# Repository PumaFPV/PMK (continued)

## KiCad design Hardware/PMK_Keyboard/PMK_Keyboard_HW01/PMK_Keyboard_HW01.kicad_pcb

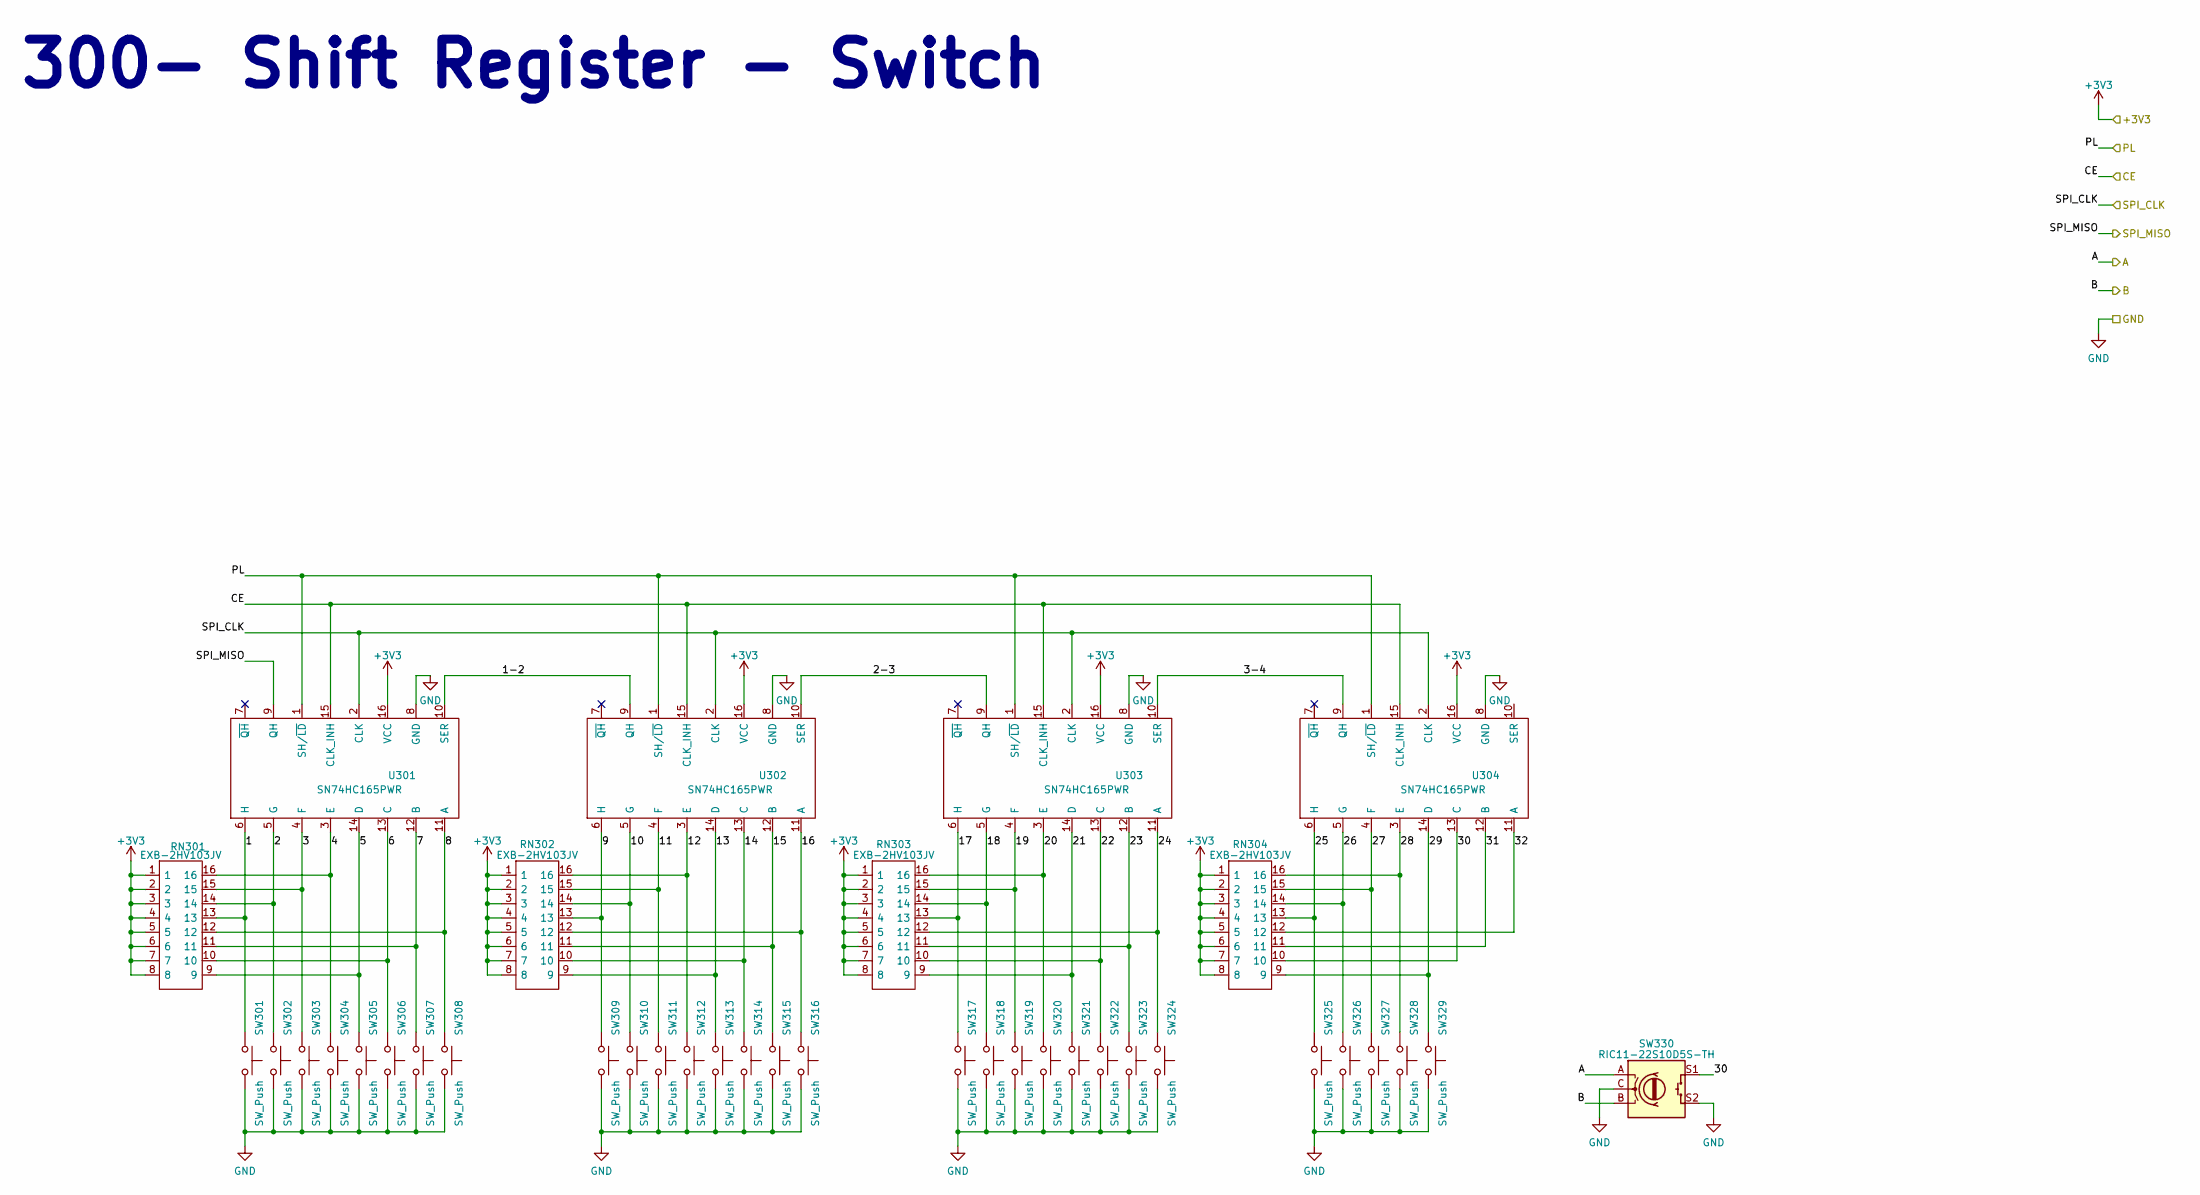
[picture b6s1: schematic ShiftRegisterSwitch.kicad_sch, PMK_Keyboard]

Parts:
RN301, RN302, RN303, RN304: EXB-2HV103JV; EXB2HV_1; Mouser Part Number 667-EXB-2HV103JV
SW301, SW302, SW303, SW304, SW305, SW306, SW307, SW308, SW309, SW310, SW311, SW312, SW313, SW314, SW315, SW316, SW317, SW318, SW319, SW320, SW321, SW322, SW323, SW324, SW325, SW326, SW327, SW328, SW329: SW_Push; Kailh_socket_PG1350_reversible
SW330: RIC11-22S10D5S-TH
U301, U302, U303, U304: SN74HC165PWR; SOP65P640X120-16N; Mouser Part Number 595-SN74HC165PWR

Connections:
+3V3: RN301.1, RN301.2, RN301.3, RN301.4, RN301.5, RN301.6, RN301.7, RN301.8, RN302.1, RN302.2, RN302.3, RN302.4, RN302.5, RN302.6, RN302.7, RN302.8, RN303.1, RN303.2, RN303.3, RN303.4, RN303.5, RN303.6, RN303.7, RN303.8, RN304.1, RN304.2, RN304.3, RN304.4, RN304.5, RN304.6, RN304.7, RN304.8, U301.16 (VCC), U302.16 (VCC), U303.16 (VCC), U304.16 (VCC); also elsewhere on the board
/100- PSoM/A: SW330.A; also elsewhere on the board
/100- PSoM/B: SW330.B; also elsewhere on the board
/100- PSoM/PL: U301.1 (SH/~LD), U302.1 (SH/~LD), U303.1 (SH/~LD), U304.1 (SH/~LD); also elsewhere on the board
/100- PSoM/SPI_CLK: U301.2 (CLK), U302.2 (CLK), U303.2 (CLK), U304.2 (CLK); also elsewhere on the board
/100- PSoM/SPI_MISO: U301.9 (QH); also elsewhere on the board
/100- PSoM/SR_CE: U301.15 (CLK_INH), U302.15 (CLK_INH), U303.15 (CLK_INH), U304.15 (CLK_INH); also elsewhere on the board
/300- Shift Register - Switch/1: RN301.13, SW301.1, U301.6 (H)
/300- Shift Register - Switch/1-2: U301.10 (SER), U302.9 (QH)
/300- Shift Register - Switch/2: RN301.14, SW302.1, U301.5 (G)
/300- Shift Register - Switch/2-3: U302.10 (SER), U303.9 (QH)
/300- Shift Register - Switch/3: RN301.15, SW303.1, U301.4 (F)
/300- Shift Register - Switch/3-4: U303.10 (SER), U304.9 (QH)
/300- Shift Register - Switch/4: RN301.16, SW304.1, U301.3 (E)
/300- Shift Register - Switch/5: RN301.9, SW305.1, U301.14 (D)
/300- Shift Register - Switch/6: RN301.10, SW306.1, U301.13 (C)
/300- Shift Register - Switch/7: RN301.11, SW307.1, U301.12 (B)
/300- Shift Register - Switch/8: RN301.12, SW308.1, U301.11 (A)
/300- Shift Register - Switch/9: RN302.13, SW309.1, U302.6 (H)
/300- Shift Register - Switch/10: RN302.14, SW310.1, U302.5 (G)
/300- Shift Register - Switch/11: RN302.15, SW311.1, U302.4 (F)
/300- Shift Register - Switch/12: RN302.16, SW312.1, U302.3 (E)
/300- Shift Register - Switch/13: RN302.9, SW313.1, U302.14 (D)
/300- Shift Register - Switch/14: RN302.10, SW314.1, U302.13 (C)
/300- Shift Register - Switch/15: RN302.11, SW315.1, U302.12 (B)
/300- Shift Register - Switch/16: RN302.12, SW316.1, U302.11 (A)
/300- Shift Register - Switch/17: RN303.13, SW317.1, U303.6 (H)
/300- Shift Register - Switch/18: RN303.14, SW318.1, U303.5 (G)
/300- Shift Register - Switch/19: RN303.15, SW319.1, U303.4 (F)
/300- Shift Register - Switch/20: RN303.16, SW320.1, U303.3 (E)
/300- Shift Register - Switch/21: RN303.9, SW321.1, U303.14 (D)
/300- Shift Register - Switch/22: RN303.10, SW322.1, U303.13 (C)
/300- Shift Register - Switch/23: RN303.11, SW323.1, U303.12 (B)
/300- Shift Register - Switch/24: RN303.12, SW324.1, U303.11 (A)
/300- Shift Register - Switch/25: RN304.13, SW325.1, U304.6 (H)
/300- Shift Register - Switch/26: RN304.14, SW326.1, U304.5 (G)
/300- Shift Register - Switch/27: RN304.15, SW327.1, U304.4 (F)
/300- Shift Register - Switch/28: RN304.16, SW328.1, U304.3 (E)
/300- Shift Register - Switch/29: RN304.9, SW329.1, U304.14 (D)
/300- Shift Register - Switch/30: RN304.10, SW330.S1, U304.13 (C)
/300- Shift Register - Switch/31: RN304.11, U304.12 (B)
/300- Shift Register - Switch/32: RN304.12, U304.11 (A)
GND: SW301.2, SW302.2, SW303.2, SW304.2, SW305.2, SW306.2, SW307.2, SW308.2, SW309.2, SW310.2, SW311.2, SW312.2, SW313.2, SW314.2, SW315.2, SW316.2, SW317.2, SW318.2, SW319.2, SW320.2, SW321.2, SW322.2, SW323.2, SW324.2, SW325.2, SW326.2, SW327.2, SW328.2, SW329.2, SW330.C, SW330.S2, U301.8 (GND), U302.8 (GND), U303.8 (GND), U304.8 (GND); also elsewhere on the board

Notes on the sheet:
300- Shift Register - Switch

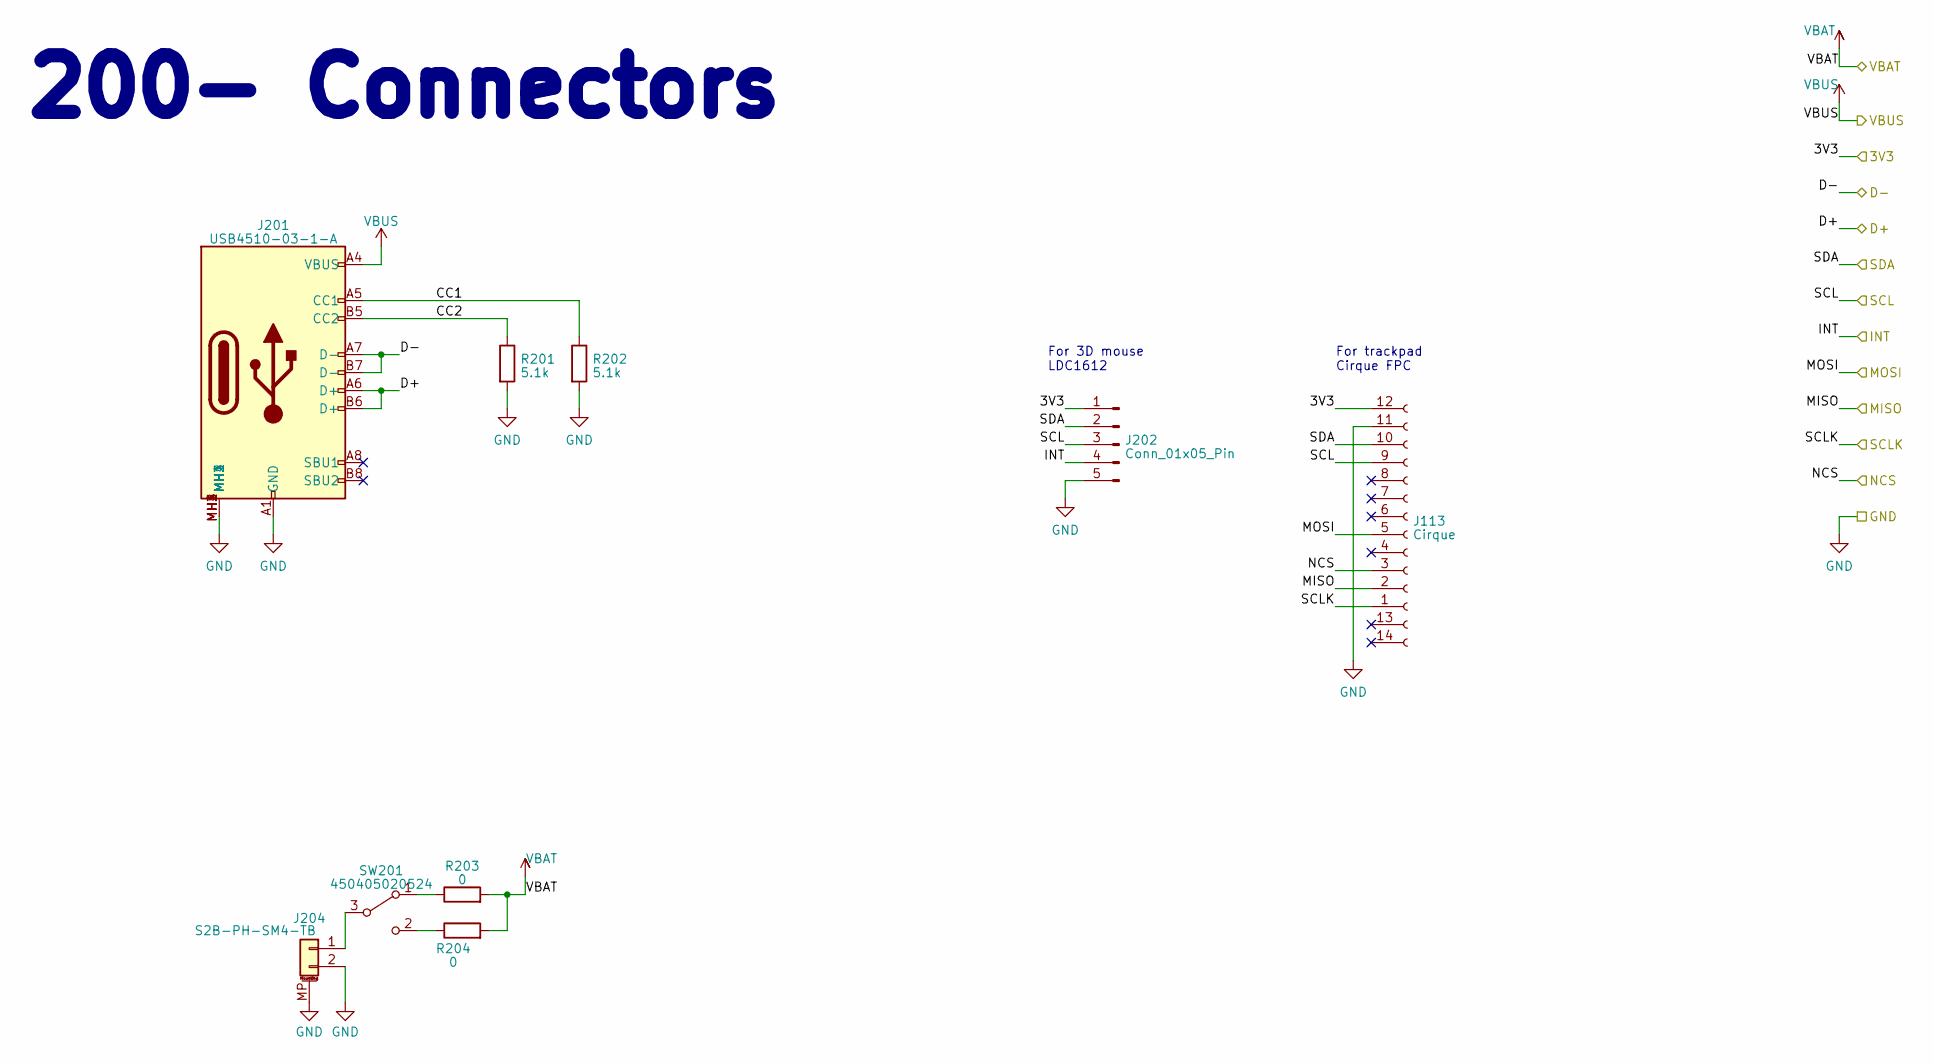
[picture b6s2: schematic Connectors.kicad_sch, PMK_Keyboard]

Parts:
J113: Cirque; Cirque trackpad
J201: USB4510-03-1-A; USB4510031A; Mouser Part Number 640-USB4510031A
J202: Conn_01x05_Pin; SMD_CONN_01x5_1.5mm
J204: S2B-PH-SM4-TB; JST_PH_S2B-PH-SM4-TB_1x02-1MP_P2.00mm_Horizontal_DUALSIDE
R201, R202: 5.1k; R_0201_0603Metric
R203, R204: 0; R_0201_0603Metric
SW201: 450405020524; 450405020524_DUALSIDE

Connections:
+3V3: J202.1; also elsewhere on the board
/100- PSoM/D+: J201.A6 (D+), J201.B6 (D+); also elsewhere on the board
/100- PSoM/D-: J201.A7 (D-), J201.B7 (D-); also elsewhere on the board
/100- PSoM/INT: J202.4; also elsewhere on the board
/100- PSoM/SCL: J202.3; also elsewhere on the board
/100- PSoM/SDA: J202.2; also elsewhere on the board
/200- Connectors/CC1: J201.A5 (CC1), R202.1
/200- Connectors/CC2: J201.B5 (CC2), R201.1
/VBAT: R203.2, R204.2; also elsewhere on the board
GND: J201.A1 (GND), J201.A12 (GND), J201.B1 (GND), J201.B12 (GND), J201.MH1, J201.MH2, J201.MH3, J201.MH4, J202.5, J204.2, J204.MP (MountPin), R201.2, R202.2; also elsewhere on the board
unnamed: J204.1, SW201.3 (B)
unnamed: R203.1, SW201.1 (A)
unnamed: R204.1, SW201.2 (C)
VBUS: J201.A4 (VBUS), J201.A9 (VBUS), J201.B4 (VBUS), J201.B9 (VBUS); also elsewhere on the board

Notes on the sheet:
200- Connectors
For trackpad Cirque FPC
For 3D mouse LDC1612

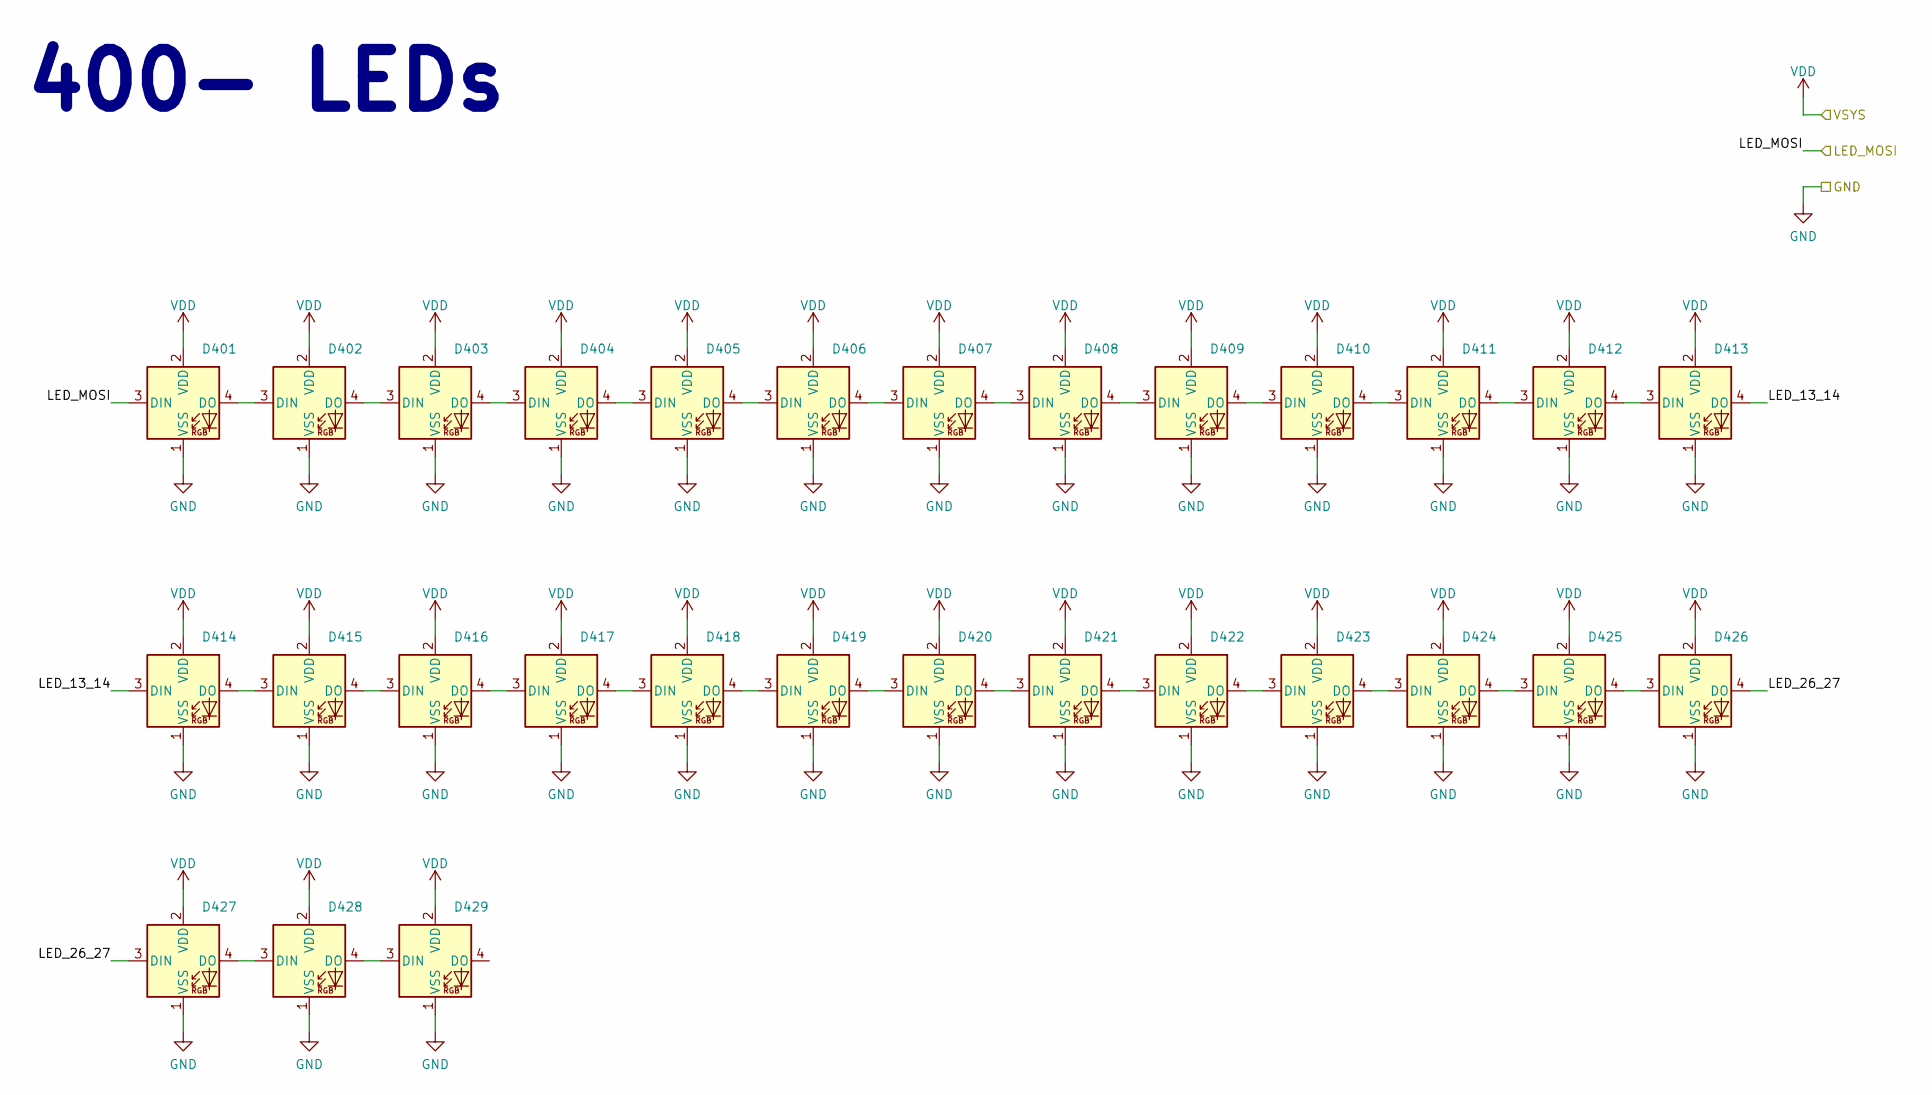
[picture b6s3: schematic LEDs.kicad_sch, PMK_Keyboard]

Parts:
D401, D402, D403, D404, D405, D406, D407, D408, D409, D410, D411, D412, D413, D414, D415, D416, D417, D418, D419, D420, D421, D422, D423, D424, D425, D426, D427, D428, D429: YF923_2020_WS2812_LED; YF923_2020_WS2812_LED_DUALSIDE

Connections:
/100- PSoM/LED_MOSI: D401.3 (DIN); also elsewhere on the board
/400- LEDs/LED_13_14: D413.4 (DO), D414.3 (DIN)
/400- LEDs/LED_26_27: D426.4 (DO), D427.3 (DIN)
GND: D401.1 (VSS), D402.1 (VSS), D403.1 (VSS), D404.1 (VSS), D405.1 (VSS), D406.1 (VSS), D407.1 (VSS), D408.1 (VSS), D409.1 (VSS), D410.1 (VSS), D411.1 (VSS), D412.1 (VSS), D413.1 (VSS), D414.1 (VSS), D415.1 (VSS), D416.1 (VSS), D417.1 (VSS), D418.1 (VSS), D419.1 (VSS), D420.1 (VSS), D421.1 (VSS), D422.1 (VSS), D423.1 (VSS), D424.1 (VSS), D425.1 (VSS), D426.1 (VSS), D427.1 (VSS), D428.1 (VSS), D429.1 (VSS); also elsewhere on the board
unnamed: D401.4 (DO), D402.3 (DIN)
unnamed: D402.4 (DO), D403.3 (DIN)
unnamed: D403.4 (DO), D404.3 (DIN)
unnamed: D404.4 (DO), D405.3 (DIN)
unnamed: D405.4 (DO), D406.3 (DIN)
unnamed: D406.4 (DO), D407.3 (DIN)
unnamed: D407.4 (DO), D408.3 (DIN)
unnamed: D408.4 (DO), D409.3 (DIN)
unnamed: D409.4 (DO), D410.3 (DIN)
unnamed: D410.4 (DO), D411.3 (DIN)
unnamed: D411.4 (DO), D412.3 (DIN)
unnamed: D412.4 (DO), D413.3 (DIN)
unnamed: D414.4 (DO), D415.3 (DIN)
unnamed: D415.4 (DO), D416.3 (DIN)
unnamed: D416.4 (DO), D417.3 (DIN)
unnamed: D417.4 (DO), D418.3 (DIN)
unnamed: D418.4 (DO), D419.3 (DIN)
unnamed: D419.4 (DO), D420.3 (DIN)
unnamed: D420.4 (DO), D421.3 (DIN)
unnamed: D421.4 (DO), D422.3 (DIN)
unnamed: D422.4 (DO), D423.3 (DIN)
unnamed: D423.4 (DO), D424.3 (DIN)
unnamed: D424.4 (DO), D425.3 (DIN)
unnamed: D425.4 (DO), D426.3 (DIN)
unnamed: D427.4 (DO), D428.3 (DIN)
unnamed: D428.4 (DO), D429.3 (DIN)
VDD: D401.2 (VDD), D402.2 (VDD), D403.2 (VDD), D404.2 (VDD), D405.2 (VDD), D406.2 (VDD), D407.2 (VDD), D408.2 (VDD), D409.2 (VDD), D410.2 (VDD), D411.2 (VDD), D412.2 (VDD), D413.2 (VDD), D414.2 (VDD), D415.2 (VDD), D416.2 (VDD), D417.2 (VDD), D418.2 (VDD), D419.2 (VDD), D420.2 (VDD), D421.2 (VDD), D422.2 (VDD), D423.2 (VDD), D424.2 (VDD), D425.2 (VDD), D426.2 (VDD), D427.2 (VDD), D428.2 (VDD), D429.2 (VDD); also elsewhere on the board

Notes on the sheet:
400- LEDs

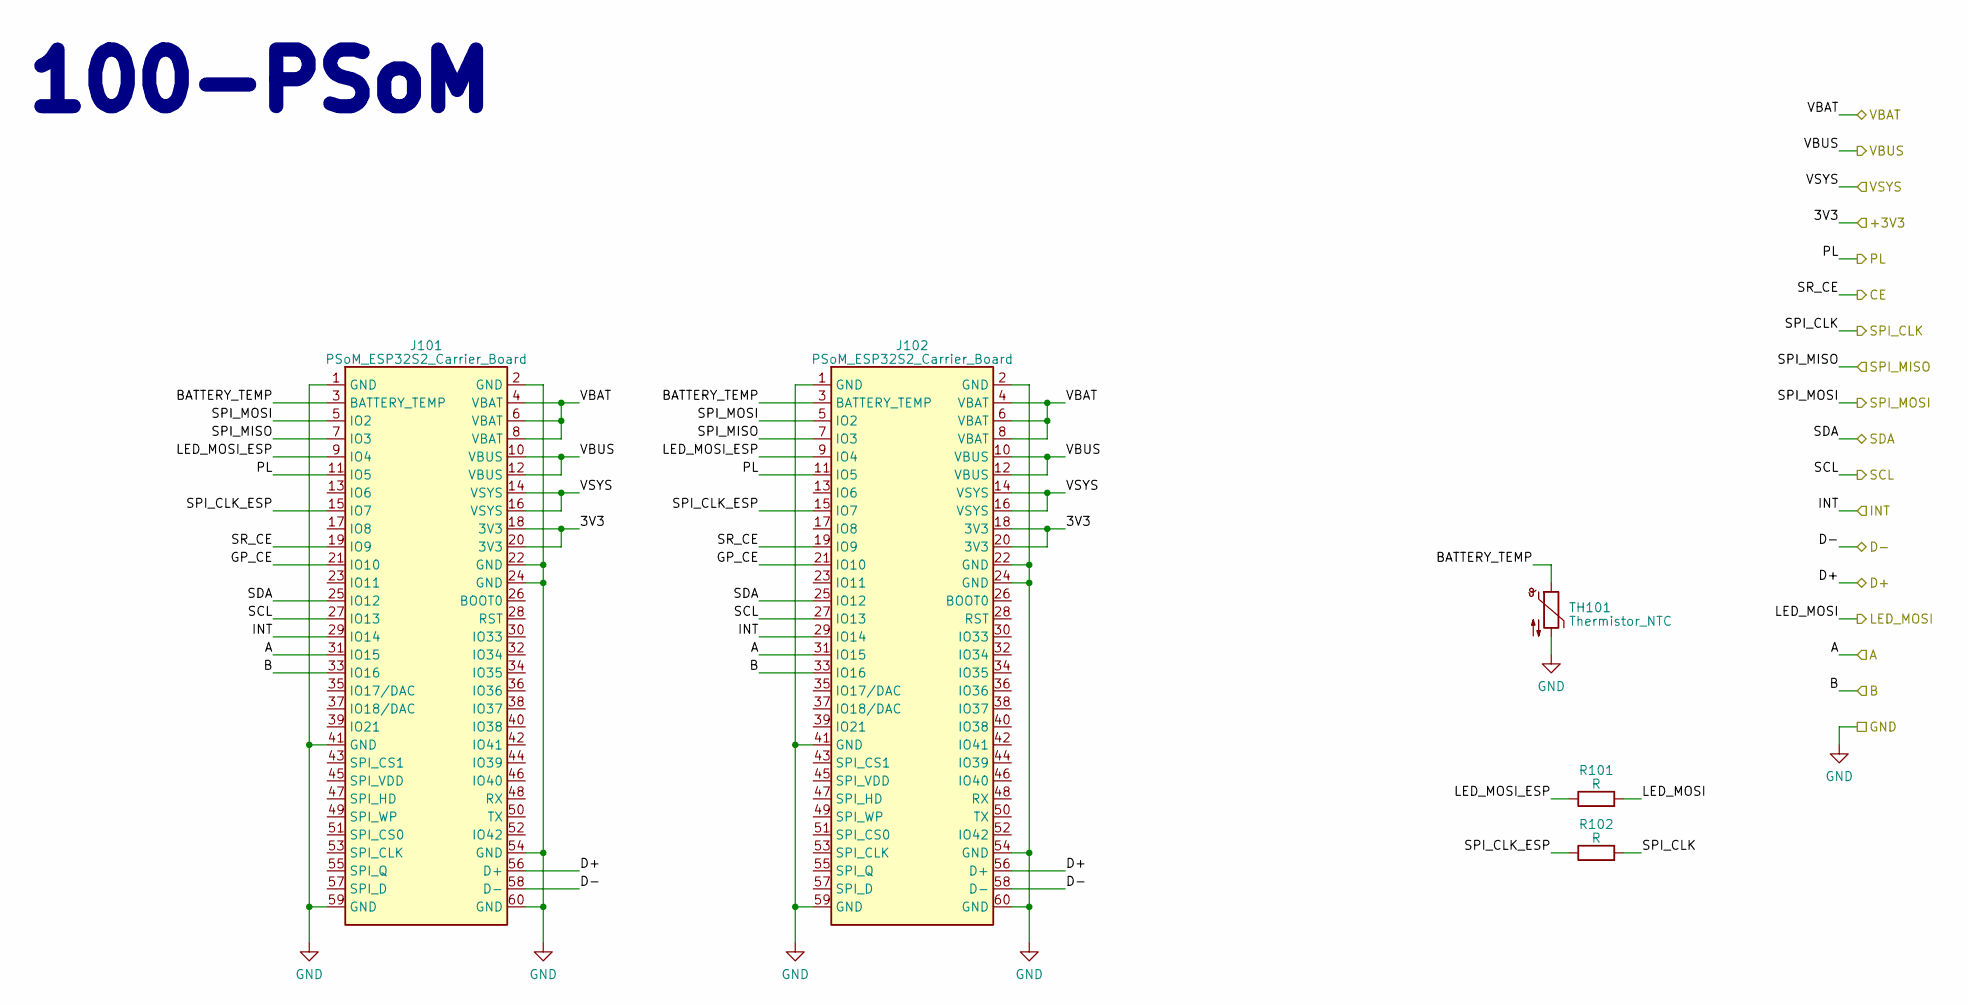
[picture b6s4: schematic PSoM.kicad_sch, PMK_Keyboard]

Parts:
J101, J102: PSoM_ESP32S2_Carrier_Board; PSoM_ESP32S2_00
R101, R102: R; R_0402_1005Metric
TH101: Thermistor_NTC; R_0402_1005Metric

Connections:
+3V3: J101.18 (3V3), J101.20 (3V3), J102.18 (3V3), J102.20 (3V3); also elsewhere on the board
/100- PSoM/A: J101.31 (IO15), J102.31 (IO15); also elsewhere on the board
/100- PSoM/B: J101.33 (IO16), J102.33 (IO16); also elsewhere on the board
/100- PSoM/BATTERY_TEMP: J101.3 (BATTERY_TEMP), J102.3 (BATTERY_TEMP), TH101.1
/100- PSoM/D+: J101.56 (D+), J102.56 (D+); also elsewhere on the board
/100- PSoM/D-: J101.58 (D-), J102.58 (D-); also elsewhere on the board
/100- PSoM/GP_CE: J101.21 (IO10), J102.21 (IO10)
/100- PSoM/INT: J101.29 (IO14), J102.29 (IO14); also elsewhere on the board
/100- PSoM/LED_MOSI: R101.2; also elsewhere on the board
/100- PSoM/LED_MOSI_ESP: J101.9 (IO4), J102.9 (IO4), R101.1
/100- PSoM/PL: J101.11 (IO5), J102.11 (IO5); also elsewhere on the board
/100- PSoM/SCL: J101.27 (IO13), J102.27 (IO13); also elsewhere on the board
/100- PSoM/SDA: J101.25 (IO12), J102.25 (IO12); also elsewhere on the board
/100- PSoM/SPI_CLK: R102.2; also elsewhere on the board
/100- PSoM/SPI_CLK_ESP: J101.15 (IO7), J102.15 (IO7), R102.1
/100- PSoM/SPI_MISO: J101.7 (IO3), J102.7 (IO3); also elsewhere on the board
/100- PSoM/SPI_MOSI: J101.5 (IO2), J102.5 (IO2); also elsewhere on the board
/100- PSoM/SR_CE: J101.19 (IO9), J102.19 (IO9); also elsewhere on the board
/VBAT: J101.4 (VBAT), J101.6 (VBAT), J101.8 (VBAT), J102.4 (VBAT), J102.6 (VBAT), J102.8 (VBAT); also elsewhere on the board
GND: J101.1 (GND), J101.2 (GND), J101.22 (GND), J101.24 (GND), J101.41 (GND), J101.54 (GND), J101.59 (GND), J101.60 (GND), J102.1 (GND), J102.2 (GND), J102.22 (GND), J102.24 (GND), J102.41 (GND), J102.54 (GND), J102.59 (GND), J102.60 (GND), TH101.2; also elsewhere on the board
VBUS: J101.10 (VBUS), J101.12 (VBUS), J102.10 (VBUS), J102.12 (VBUS); also elsewhere on the board
VDD: J101.14 (VSYS), J101.16 (VSYS), J102.14 (VSYS), J102.16 (VSYS); also elsewhere on the board

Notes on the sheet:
100-PSoM

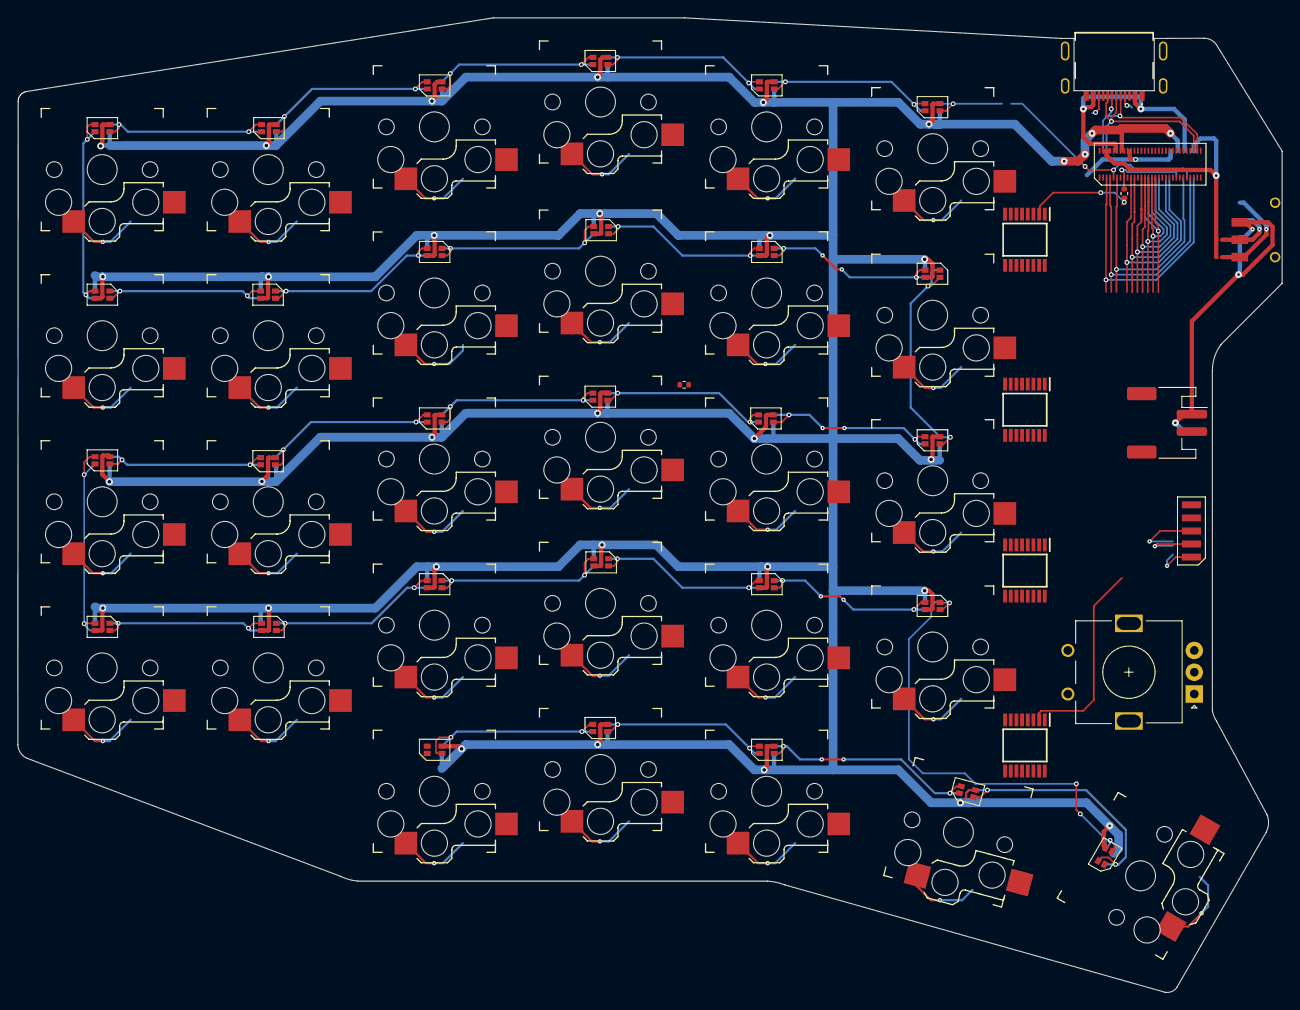
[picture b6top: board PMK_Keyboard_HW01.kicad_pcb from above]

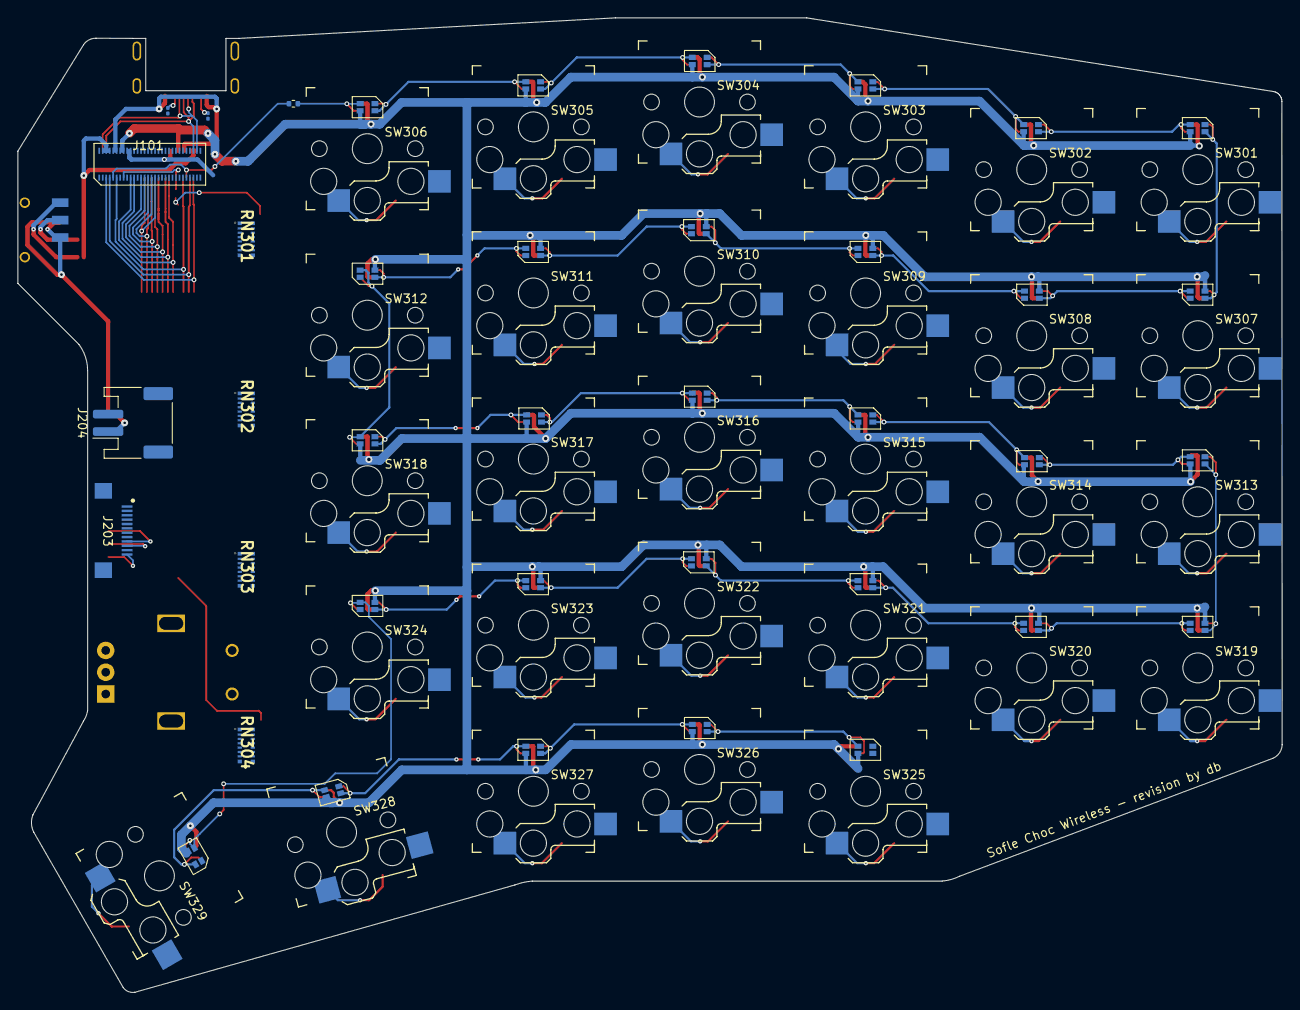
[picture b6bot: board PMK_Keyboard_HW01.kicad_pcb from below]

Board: 2 copper layers, 145.0 x 111.8 mm, 81 parts (10 on the bottom side), 90 nets.

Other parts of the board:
J203: Cirque; Cirque trackpad

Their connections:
+3V3: J203.12; also elsewhere on the board
/100- PSoM/SCL: J203.9; also elsewhere on the board
/100- PSoM/SDA: J203.10; also elsewhere on the board
/100- PSoM/SPI_CLK: J203.1; also elsewhere on the board
/100- PSoM/SPI_MISO: J203.2; also elsewhere on the board
/100- PSoM/SPI_MOSI: J203.5; also elsewhere on the board
/100- PSoM/SR_CE: J203.3; also elsewhere on the board
GND: J203.11; also elsewhere on the board

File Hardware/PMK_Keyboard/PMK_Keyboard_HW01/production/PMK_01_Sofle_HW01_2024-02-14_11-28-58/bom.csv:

Designator,Footprint,Quantity,Value,LCSC Part #
"D401, D402, D403, D404, D405, D406, D407, D408, D409, D410, D411, D412, D413, D414, D415, D416, D417, D418, D419, D420, D421, D422, D423, D424, D425, D426, D427, D428, D429",YF923_2020_WS2812_LED_DUALSIDE,29,YF923_2020_WS2812_LED,
"J101, J102",PSoM_ESP32S2_00,2,PSoM_ESP32S2_Carrier_Board,
J201,USB4510031A,1,USB4510-03-1-A,
J202,SMD_CONN_01x5_1.5mm,1,Conn_01x05_Pin,
J204,JST_PH_S2B-PH-SM4-TB_1x02-1MP_P2.00mm_Horizontal_DUALSIDE,1,S2B-PH-SM4-TB,
J301,5051101292,1,505110-1292,
"R101, R102",0402,2,R,
"R201, R202",0402,2,5.1k,
"R203, R204",0402,2,0,
"RN301, RN302, RN303, RN304",EXB2HV_1,4,EXB-2HV103JV,
SW201,450405020524_DUALSIDE,1,450405020524,
"SW301, SW302, SW303, SW304, SW305, SW306, SW307, SW308, SW309, SW310, SW311, SW312, SW313, SW314, SW315, SW316, SW317, SW318, SW319, SW320, SW321, SW322, SW323, SW324, SW325, SW326, SW327, SW328, SW329",Kailh_socket_PG1350_reversible,29,SW_Push,
SW330,RIC11-22S10D5S-TH,1,RIC11-22S10D5S-TH,
"TH101, TH102",0402,2,Thermistor_NTC,
"U301, U302, U303, U304",SOP65P640X120-16N,4,SN74HC165PWR,
